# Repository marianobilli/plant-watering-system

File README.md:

# Plant Watering System

An automated 6-plant watering system built on an ESP32-S3 (YD-ESP32-23), designed around the failures of typical DIY irrigation projects: corroding sensors, constant over-watering, no verification that watering worked.

- **6 independent stations:** capacitive moisture sensor + 12 V peristaltic pump each
- **Two-phase watering cycle:** dry cycle (check every N hours, water only at the minimum threshold) then incremental watering with soak time until the target is reached
- **Failsafes:** a plant is stopped and flagged if moisture does not rise after a dose, if the sensor reads shorted/disconnected, or if a float switch reports a low reservoir; one pump runs at a time
- **Sensor longevity:** sensors are only powered (DIS pin) for the ~1 s of each reading
- **Local UI:** 128×64 OLED + rotary encoder + Confirm/Back buttons; all settings persist in flash (NVS)

Firmware and tests are PlatformIO/Arduino; the board is designed in KiCad. Plants start **disabled** on a fresh board: enable each one from the menu after calibrating its sensor and pump.

## Quick start

```bash
pip install platformio            # or use the PlatformIO VS Code extension
# Plug into the board's UART USB-C connector (not the one labelled USB),
# then set upload_port in platformio.ini (e.g. COM3).
pio run -t upload                 # build + flash
pio device monitor                # serial log @ 115200
pio test -e native                # watering-logic tests on your computer (needs gcc/clang)
pio test -e yd_esp32_23           # same tests on the board
```

First-time setup from the OLED menu: **Menu → Plant n → Cal sensor** (air, then water), **Cal pump** (run 30 s into a cup, enter the mL), set Target / Min / Water mL / Soak / Check h, then switch **Enabled** on.

## Repository layout

```
platformio.ini            Board/env config (yd_esp32_23 = firmware, native = host tests)
partitions/               16 MB partition table (do not edit)
src/main.cpp              Hardware glue: sensors, pumps, float switch, OLED menu, NVS config
include/pins.h            Pin map (mirrors the schematic)
lib/PlantLogic/           Hardware-free per-plant state machine + helpers (unit-tested)
lib/RotaryEncoder/        Quadrature encoder driver
test/test_plant_logic/    Unity tests for lib/PlantLogic
hardware/
  BOM.md                  Bill of materials, derived from the schematic
  pcb_print_1to1_A4.pdf   1:1 printable board drawing (A4) for test-fitting parts and the enclosure
  kicad/                  plant_watering.kicad_{sch,pcb,pro} + project symbol/footprint libs
docs/
  WATERING_LOGIC.md       The two-phase algorithm with worked examples
  lessons_learned.md      Research from 50+ failed DIY projects
  archive/                Superseded Arduino UNO R4 POC / single-plant monitor docs
```

## Pin map

| Function | GPIO |
|----------|------|
| Sensors S1–S6 (ADC1) | 1, 2, 7, 8, 9, 10 |
| Sensor DIS (shared, LOW = on) | 11 |
| Pumps 1–6 (MOSFET gates) | 15, 17, 39, 12, 16, 18 |
| Float switch (optional, LOW = reservoir low) | 47 |
| OLED SDA / SCL | 14 / 13 |
| Encoder A / B / push | 5 / 4 / 6 |
| Confirm / Back | 21 / 38 |

> [!WARNING]
> **Leave the ESP board's `IN-OUT` solder jumper open** (no solder bridge). The PCB powers the ESP from the charger through `5Vin` (footprint pad 21, left header, 2nd from the bottom; not GPIO21, which is pad 40). With the jumper open, the on-board diode keeps that 5 V from flowing back into the ESP's USB-C VBUS, so a laptop can stay plugged in for flashing and monitoring while the charger is connected. Bridged, the charger and the laptop's USB 5 V are tied together and current can be pushed back into the laptop's port. If your board arrives bridged, remove the solder. Before first power-up, check with a multimeter in diode mode (board unpowered): USB VBUS → `5Vin` reads a diode drop (~0.2–0.4 V), the reverse reads open.

Header order, antenna end first (matches footprint pads 1–22 / 23–44):

| Header | Pins |
|--------|------|
| P1 (pads 1–22) | 3V3, 3V3, RST, 4, 5, 6, 7, 15, 16, 17, 18, 8, 3, 46, 9, 10, 11, 12, 13, 14, 5Vin, GND |
| P2 (pads 23–44) | GND, TX, RX, 1, 2, 42, 41, 40, 39, 38, 37, 36, 35, 0, 45, 48, 47, 21, 20, 19, GND, GND |

Sensors are on ADC1 because ADC2 cannot be used while WiFi is active. Avoid IO0, 3, 45, 46 (strapping), 19/20 (USB) and 35–37 (octal PSRAM).

## Hardware

See [hardware/BOM.md](hardware/BOM.md). Power is a single 5 V / 2 A USB-C charger, plugged into a panel-mount USB-C socket on the enclosure ([photo](docs/usb-connector.png)) whose two wires (V+, V−) go to J1 (JST-XH 2-pin); an on-board MT3608 boost module makes 12 V for the pumps. Open `hardware/kicad/plant_watering.kicad_pro` in KiCad 10. To order the PCB, see [docs/MANUFACTURING.md](docs/MANUFACTURING.md) (Gerber export, order settings, per-maker hole sizes).

**UI module:** 1.3" 128×64 OLED + EC11 encoder + Back/Confirm buttons on one 64.9 × 35 mm board ([dimensions](docs/oled-rotary-encoder-dimensions.jpg)).

It mounts face-up to the left of the ESP32, turned 90° (header towards the ESP): its 9-pin header plugs into J2 (a 1×9 2.54 mm female socket) and four M3 brass standoffs screw it down through the matching holes in the J2 footprint. An 8.5 mm socket plus the header's 2.5 mm plastic spacer puts the module ~11 mm up, so use M3 × 11 mm standoffs (or 10 mm + a washer); measure your socket and header first. The module's male header must point out of its back; if the pins stick out of the display side, resolder the header. The socket's pin order matches the module silkscreen (CON SDA SCL PSH TRA TRB BAK GND VCC); VCC is 3V3.

**1:1 printout:** [hardware/pcb_print_1to1_A4.pdf](hardware/pcb_print_1to1_A4.pdf) shows the board outline, pads with real drill sizes, silkscreen and part outlines at true scale on A4. Use it to check the space the board needs wherever it will be mounted (enclosure, standoffs, cable and connector clearance, access to the ESP's USB-C port) and to test-fit parts before ordering:

1. Print on A4 at **Actual size / 100 %** (never "Fit to page").
2. Check the scale: the board outline must measure **143 × 112 mm**, and the two ESP pin rows 25.4 mm apart.
3. Glue it onto cardboard or foam board, pierce the pads with a pin and push in the real parts; lay it in the enclosure to check the mounting holes and cable routes.

Regenerate it after any PCB change (from `hardware/kicad/`):
`kicad-cli pcb export pdf --mode-single -l Edge.Cuts,F.Mask,F.SilkS,F.Fab --sp --black-and-white --ibt --scale 1 -o ../pcb_print_1to1_A4.pdf plant_watering.kicad_pcb`

## Test rig (3D print)

Before the real enclosure, an open printed tray holds the PCB and all six pumps so the whole system can be wired and run on the bench. The PCB sits on posts with the pump motors underneath it; two pumps mount on each side and two at the back, so the front with the display and controls stays clear. There is no lid and no reservoir: put the inlet tubes in a bucket.

**Ordering or printing:** use **`case/print/test_rig.stl`** (or `.step`), 1:1 in millimetres, one piece, 152 × 122 × 42 mm, about 90 cm³ (≈ 110 g).

| Process and material | Verdict |
|---|---|
| **FDM, PETG** | Best: tough and cheap. PLA also works, nothing on this part flexes |
| MJF or SLS nylon, PA12 | Fine if ordering from a service |
| SLA / resin | Avoid, the thin walls get brittle |

### Printing on FDM: tell the printer this

The part is designed to print **without supports** in the orientation it is in the file.

| Setting | Value |
|---|---|
| **Orientation** | Base plate flat on the bed, walls and posts pointing up, as in the file |
| **Supports** | **Off.** The motor slots are open at the top and the base windows go through, so there is nothing to support |
| Layer / nozzle | 0.2 mm / 0.4 mm |
| Perimeters | 4 (the 4 mm walls and the 8 mm posts then come out nearly solid) |
| Infill | 20 to 30 % |
| Brim | Optional; helps the tall, thin posts if the bed adhesion is poor |

**Hardware to buy with it:**

| Qty | Part |
|----:|------|
| 12 | M3 male–male rubber anti-vibration mounts, Ø8 × 8 mm ("M3 rubber shock absorber") |
| 24 | M3 nuts |
| 5 | M3 heat-set inserts, 3 mm long × 4.2 mm OD, and 5 × M3 × 5 screws for the PCB |
| 6 | 3 mm foam tape pads, about 16 × 12 mm |
| 4 | Stick-on rubber feet |

**Assembly**

1. Press the heat-set inserts into the five posts with a soldering iron (only MH1–MH4 and MH6 have posts; the side motors pass where MH5 and MH7 would be).
2. Screw a rubber mount into each wall hole, with a nut on the inside. Drop each pump's motor into its U-slot from above, lay the bracket on the mounts' outer studs and fit the nuts. The slot is 3.5 mm wider than the motor can on each side, so the motor touches nothing but rubber. A plain M3 screw and nut also fits, without the vibration isolation.
3. Stick a foam pad on the small block under each motor's free end, so the motor doesn't sag on the rubber.
4. Trim the PCB's through-hole leads to **2 mm or less** on the underside: the motors run 2.5 mm under the trimmed joints. Then screw the PCB onto the posts, display at the open front.
5. Pump numbering follows J9–J14, going round from the front left: **P1, P2** on the left wall (front, back), **P3, P4** on the back wall (left, right), **P5, P6** on the right wall (back, front). The tube stubs point up.

**Regenerating the rig.** The rig is generated by `case/test_rig.py` with [build123d](https://build123d.readthedocs.io/), reading the mounting-hole positions from the KiCad board. Running it rewrites `case/print/`, writes every format to `case/out/` (with a full assembly STEP) and checks the rig and both pump mountings (rubber and direct) against every part on the board. It needs KiCad 10 for `kicad-cli`, Python 3 with `build123d` and `ocp_vscode`, and optionally the *OCP CAD Viewer* extension in VS Code (Ctrl+K V) to see the assembly:

```bash
pip install build123d ocp_vscode
python case/test_rig.py            # pumps on rubber mounts in the viewer
python case/test_rig.py direct     # pumps screwed flat to the walls
```

Every dimension is a parameter at the top of the script, and the pump model comes from [docs/Pump Technical Drawing Views.pdf](docs/Pump%20Technical%20Drawing%20Views.pdf).

## Common DIY mistakes this avoids

| Mistake | Solution here |
|---------|---------------|
| Resistive sensors corrode in weeks | Capacitive sensors, waterproofed with nail polish |
| Sensors always powered | DIS pin: on only while reading |
| Constant watering, root rot | Dry cycle with configurable thresholds |
| Re-watering before moisture spreads | Soak time between doses |
| No check that watering worked | Fault latched if moisture does not rise |
| Pump left running / reservoir empty | Hard 2 min cap per run, float switch stops pumping |

Details: [docs/lessons_learned.md](docs/lessons_learned.md), [docs/WATERING_LOGIC.md](docs/WATERING_LOGIC.md).

## Tuning and best practices

**Soak time** (wait after each dose before re-measuring): sandy/fast-draining soil 3–5 min, loam 5–10 min, clay/slow-draining 10–15 min. Default 5 min.

**Sensors:** capacitive only (resistive ones corrode in weeks), waterproofed with nail polish; calibrate in the real soil, not just air/water; use a TLC555-based sensor on 3.3 V systems, not NE555.

**Mechanical:** keep the reservoir **below** plant level (above it, water keeps siphoning after the pump stops); opaque tubing, 5–6 mm ID (narrower clogs); a closed-end hose with ~1 mm holes at each plant distributes more evenly than Y-splitters; flush with plain water and descale with vinegar when it clogs.

**Maintenance schedule**

| Interval | Task |
|----------|------|
| Weekly | Check reservoir level, test a pump manually, look for odd moisture readings or sensor drift |
| Monthly | Inspect tubing for algae/scale, compare readings with a finger test, check connectors for corrosion |
| Quarterly | Inspect sensor waterproofing, recalibrate if drifting, clean reservoir with vinegar, check MOSFETs/diodes |
| Yearly | **Replace peristaltic pump tubing** (it wears out), deep-clean reservoir and tubing, replace corroded sensors, test failsafes (unplugged sensor, empty reservoir) |

Act immediately if: readings disagree with the soil, a pump runs but no water flows, watering becomes erratic, or you see corrosion on a sensor or wire.

**If WiFi is added later:** the ESP32 does not reliably reconnect on its own, so check `WiFi.status()` in `loop()` and call `WiFi.reconnect()`; use a static IP, a 20 MHz router channel and better than −70 dBm signal. Keep sensors on ADC1 (ADC2 is unusable while WiFi is on). For deep sleep, wait ~500 ms after waking before reading RTC memory and use `1000000ULL` for the timer constant.

## Status

Firmware builds and the watering-logic tests pass. The hardware path (ADC readings, OLED menu, pumps) has **not yet been run on a board**. The earlier single-plant Arduino UNO R4 firmware and docs are kept in `docs/archive/` and in git history.

## TODO

### Before ordering the PCB
- [ ] Check the panel USB-C socket has 5.1 kΩ CC pull-downs built in (needed for C-to-C chargers) and verify V+/V− polarity to J1 (1 GND, 2 VBUS) before plugging in a charger
- [ ] Consider moving the ESP so its antenna overhangs the board edge (needs a full re-route); until then the copper-pour keepout under the antenna is the mitigation
- [ ] Generate Gerbers/drill files (`python hardware/fab/export_fab.py`, see [docs/MANUFACTURING.md](docs/MANUFACTURING.md)) and review them in a viewer before sending to the fab

### Bring-up
- [ ] Set the MT3608 output to **12 V with no pumps connected**, then check the +5 V and +3V3 rails
- [ ] Verify the float switch polarity and wiring (contact closes to GND when the reservoir is low; leave J15 empty if unused)
- [ ] Fit the UI module on J2 with its standoffs (height, hole alignment) and verify its wiring (OLED I2C address and driver: SH1106 vs SSD1306, encoder direction, CON/BAK buttons)
- [ ] Flash and run the firmware on the real board for the first time (the OLED menu, ADC reads, pumps and NVS are untested on hardware)
- [ ] Calibrate each sensor (air/water) and each pump (30 s into a cup); the 12-bit ADC defaults (3100 dry / 1500 wet) are only a guess
- [ ] Check ADC noise and linearity at 11 dB attenuation with the shared DIS line; tune `SENSOR_WARMUP_MS` / `SENSOR_SAMPLES` if readings drift
- [ ] Confirm one pump at a time stays within the 5 V / 2 A charger limit (boost converter input current)
- [ ] Run a monitor-only period with pumps disconnected to learn each plant's dry-down rate before enabling watering
- [ ] Test the failsafes on the bench: unplug a sensor, run a pump dry (no moisture rise), trip the float switch mid-run

### Firmware
- [ ] Run `pio test -e native` and `pio test -e yd_esp32_23` with a real compiler/board (only a one-off host build has been run so far)
- [ ] Log history (moisture per plant) to flash or serial for tuning thresholds
- [ ] Persist the timer state across power loss (checks currently restart on boot)
- [ ] WiFi + remote status/alerts (needs explicit reconnect logic, static IP, ADC1-only sensors)
- [ ] Menu extras: factory reset, per-plant names, rename `Enabled` default flow for first-time setup
- [ ] Set `upload_port` in `platformio.ini` for your machine

### Mechanical / docs
- [x] Open test rig for the PCB and six pumps (`case/test_rig.py`)
- [ ] Enclosure: electronics-and-pump lid on a food-grade 6 L reservoir (waiting on the box's measurements); ultrasonic level sensor; opaque tubing, 5–6 mm ID
- [ ] Waterproof each sensor with 2 coats of clear nail polish before use
- [ ] Write a wiring/assembly guide with photos

## License

[MIT](LICENSE)

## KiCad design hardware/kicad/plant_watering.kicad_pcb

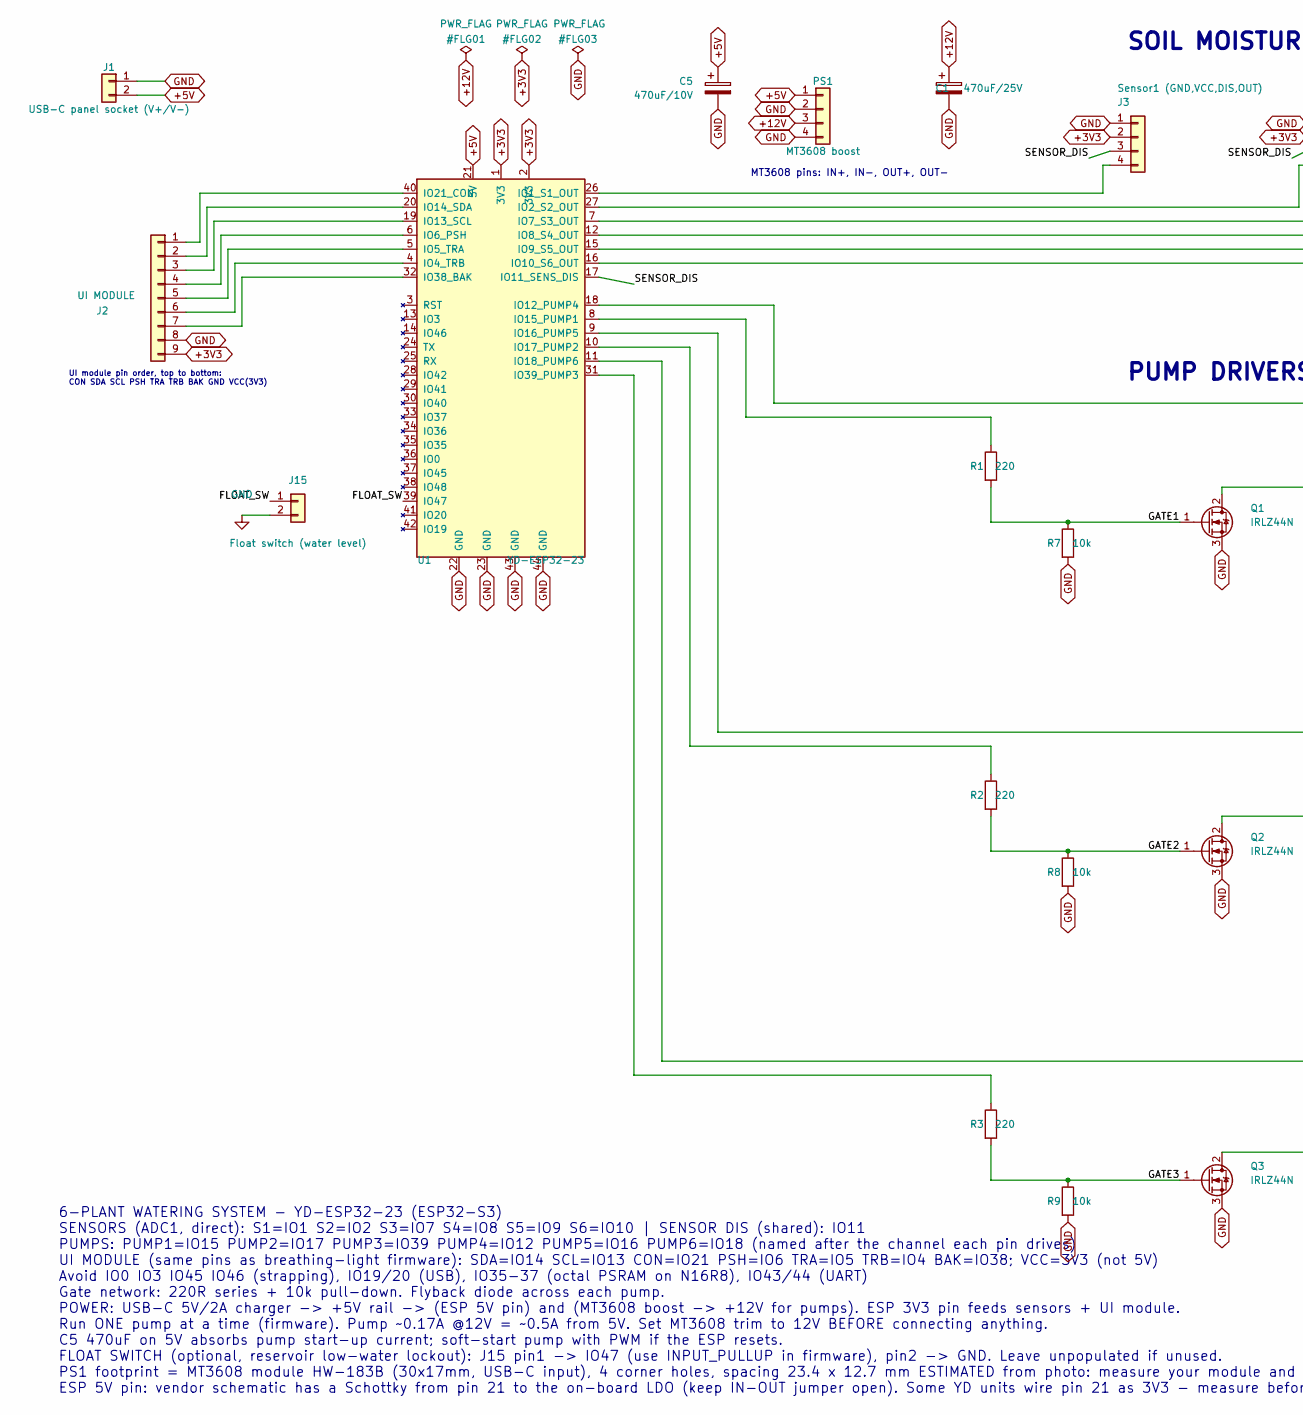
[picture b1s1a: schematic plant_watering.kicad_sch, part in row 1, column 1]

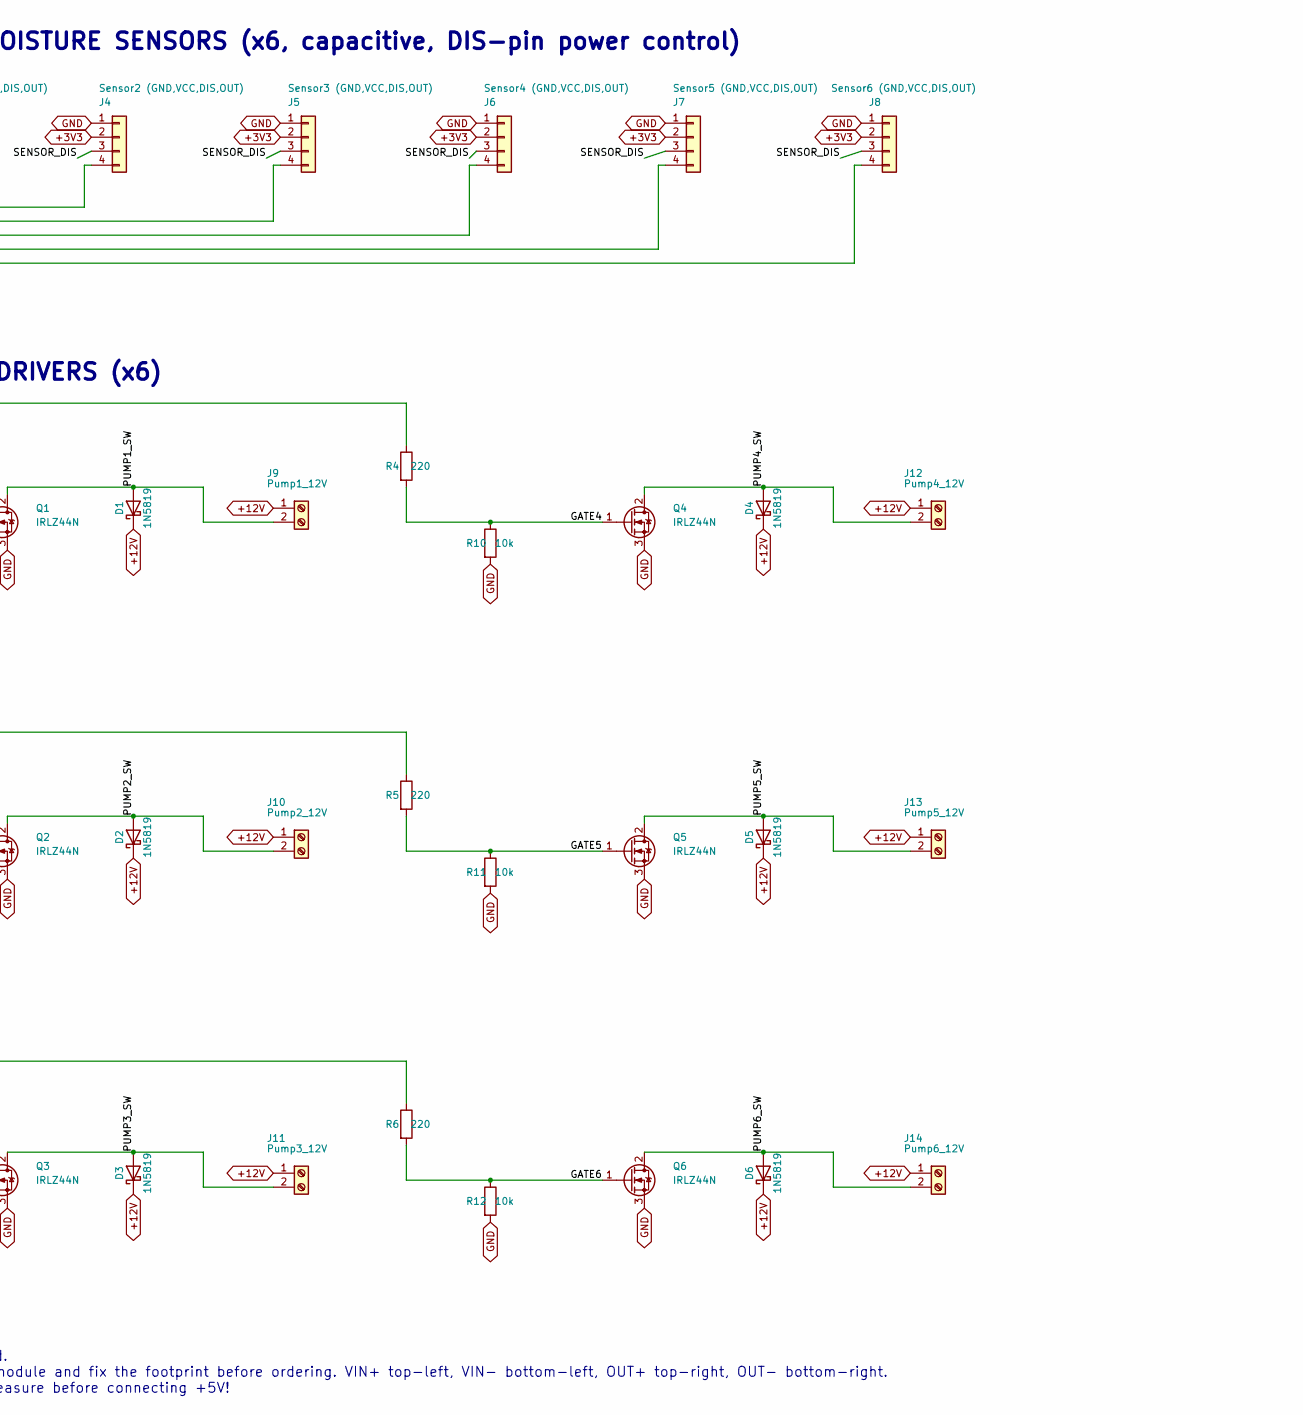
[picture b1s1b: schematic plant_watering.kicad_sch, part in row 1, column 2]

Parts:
C1: 470uF/25V; CP_Radial_D8.0mm_P3.50mm
C5: 470uF/10V; CP_Radial_D8.0mm_P3.50mm
D1, D2, D3, D4, D5, D6: 1N5819; D_DO-41_SOD81_P10.16mm_Horizontal
J1: USB-C panel socket (V+/V-); JST_XH_B2B-XH-A_1x02_P2.50mm_Vertical
J2: UI MODULE; UI_module_OLED_EC11
J3: Sensor1 (GND,VCC,DIS,OUT); JST_XH_B4B-XH-A_1x04_P2.50mm_Vertical
J4: Sensor2 (GND,VCC,DIS,OUT); JST_XH_B4B-XH-A_1x04_P2.50mm_Vertical
J5: Sensor3 (GND,VCC,DIS,OUT); JST_XH_B4B-XH-A_1x04_P2.50mm_Vertical
J6: Sensor4 (GND,VCC,DIS,OUT); JST_XH_B4B-XH-A_1x04_P2.50mm_Vertical
J7: Sensor5 (GND,VCC,DIS,OUT); JST_XH_B4B-XH-A_1x04_P2.50mm_Vertical
J8: Sensor6 (GND,VCC,DIS,OUT); JST_XH_B4B-XH-A_1x04_P2.50mm_Vertical
J9: Pump1_12V; JST_XH_B2B-XH-A_1x02_P2.50mm_Vertical
J10: Pump2_12V; JST_XH_B2B-XH-A_1x02_P2.50mm_Vertical
J11: Pump3_12V; JST_XH_B2B-XH-A_1x02_P2.50mm_Vertical
J12: Pump4_12V; JST_XH_B2B-XH-A_1x02_P2.50mm_Vertical
J13: Pump5_12V; JST_XH_B2B-XH-A_1x02_P2.50mm_Vertical
J14: Pump6_12V; JST_XH_B2B-XH-A_1x02_P2.50mm_Vertical
J15: Float switch (water level); JST_XH_B2B-XH-A_1x02_P2.50mm_Vertical
PS1: MT3608 boost; MT3608_module
Q1, Q2, Q3, Q4, Q5, Q6: IRLZ44N; TO-220-3_Vertical
R1, R2, R3, R4, R5, R6: 220; R_Axial_DIN0207_L6.3mm_D2.5mm_P10.16mm_Horizontal
R7, R8, R9, R10, R11, R12: 10k; R_Axial_DIN0207_L6.3mm_D2.5mm_P10.16mm_Horizontal
U1: YD-ESP32-23

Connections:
+3V3: J2.9, J3.2, J4.2, J5.2, J6.2, J7.2, J8.2, U1.1 (3V3), U1.2 (3V3)
+5V: C5.1, J1.2, PS1.1, U1.21 (5V)
+12V: C1.1, D1.1 (K), D2.1 (K), D3.1 (K), D4.1 (K), D5.1 (K), D6.1 (K), J9.1, J10.1, J11.1, J12.1, J13.1, J14.1, PS1.3
FLOAT_SW: J15.1, U1.39 (IO47)
GATE1: Q1.1 (G), R1.2, R7.1
GATE2: Q2.1 (G), R2.2, R8.1
GATE3: Q3.1 (G), R3.2, R9.1
GATE4: Q4.1 (G), R4.2, R10.1
GATE5: Q5.1 (G), R5.2, R11.1
GATE6: Q6.1 (G), R6.2, R12.1
GND: C1.2, C5.2, J1.1, J2.8, J3.1, J4.1, J5.1, J6.1, J7.1, J8.1, J15.2, PS1.2, PS1.4, Q1.3 (S), Q2.3 (S), Q3.3 (S), Q4.3 (S), Q5.3 (S), Q6.3 (S), R7.2, R8.2, R9.2, R10.2, R11.2, R12.2, U1.22 (GND), U1.23 (GND), U1.43 (GND), U1.44 (GND)
unnamed: J2.1, U1.40 (IO21_CON)
unnamed: J2.2, U1.20 (IO14_SDA)
unnamed: J2.3, U1.19 (IO13_SCL)
unnamed: J2.4, U1.6 (IO6_PSH)
unnamed: J2.5, U1.5 (IO5_TRA)
unnamed: J2.6, U1.4 (IO4_TRB)
unnamed: J2.7, U1.32 (IO38_BAK)
unnamed: J3.4, U1.26 (IO1_S1_OUT)
unnamed: J4.4, U1.27 (IO2_S2_OUT)
unnamed: J5.4, U1.7 (IO7_S3_OUT)
unnamed: J6.4, U1.12 (IO8_S4_OUT)
unnamed: J7.4, U1.15 (IO9_S5_OUT)
unnamed: J8.4, U1.16 (IO10_S6_OUT)
unnamed: R1.1, U1.8 (IO15_PUMP1)
unnamed: R2.1, U1.10 (IO17_PUMP2)
unnamed: R3.1, U1.31 (IO39_PUMP3)
unnamed: R4.1, U1.18 (IO12_PUMP4)
unnamed: R5.1, U1.9 (IO16_PUMP5)
unnamed: R6.1, U1.11 (IO18_PUMP6)
PUMP1_SW: D1.2 (A), J9.2, Q1.2 (D)
PUMP2_SW: D2.2 (A), J10.2, Q2.2 (D)
PUMP3_SW: D3.2 (A), J11.2, Q3.2 (D)
PUMP4_SW: D4.2 (A), J12.2, Q4.2 (D)
PUMP5_SW: D5.2 (A), J13.2, Q5.2 (D)
PUMP6_SW: D6.2 (A), J14.2, Q6.2 (D)
SENSOR_DIS: J3.3, J4.3, J5.3, J6.3, J7.3, J8.3, U1.17 (IO11_SENS_DIS)

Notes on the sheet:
6-PLANT WATERING SYSTEM - YD-ESP32-23 (ESP32-S3) SENSORS (ADC1, direct): S1=IO1 S2=IO2 S3=IO7 S4=IO8 S5=IO9 S6=IO10 | SENSOR DIS (shared): IO11 PUMPS: PUMP1=IO15 PUMP2=IO17 PUMP3=IO39 PUMP4=IO12 PUMP5=IO16 PUMP6=IO18 (named after the channel each pin drives) UI MODULE (same pins as breathing-light 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
PUMP DRIVERS (x6)
UI module pin order, top to bottom: CON SDA SCL PSH TRA TRB BAK GND VCC(3V3)
MT3608 pins: IN+, IN-, OUT+, OUT-
SOIL MOISTURE SENSORS (x6, capacitive, DIS-pin power control)

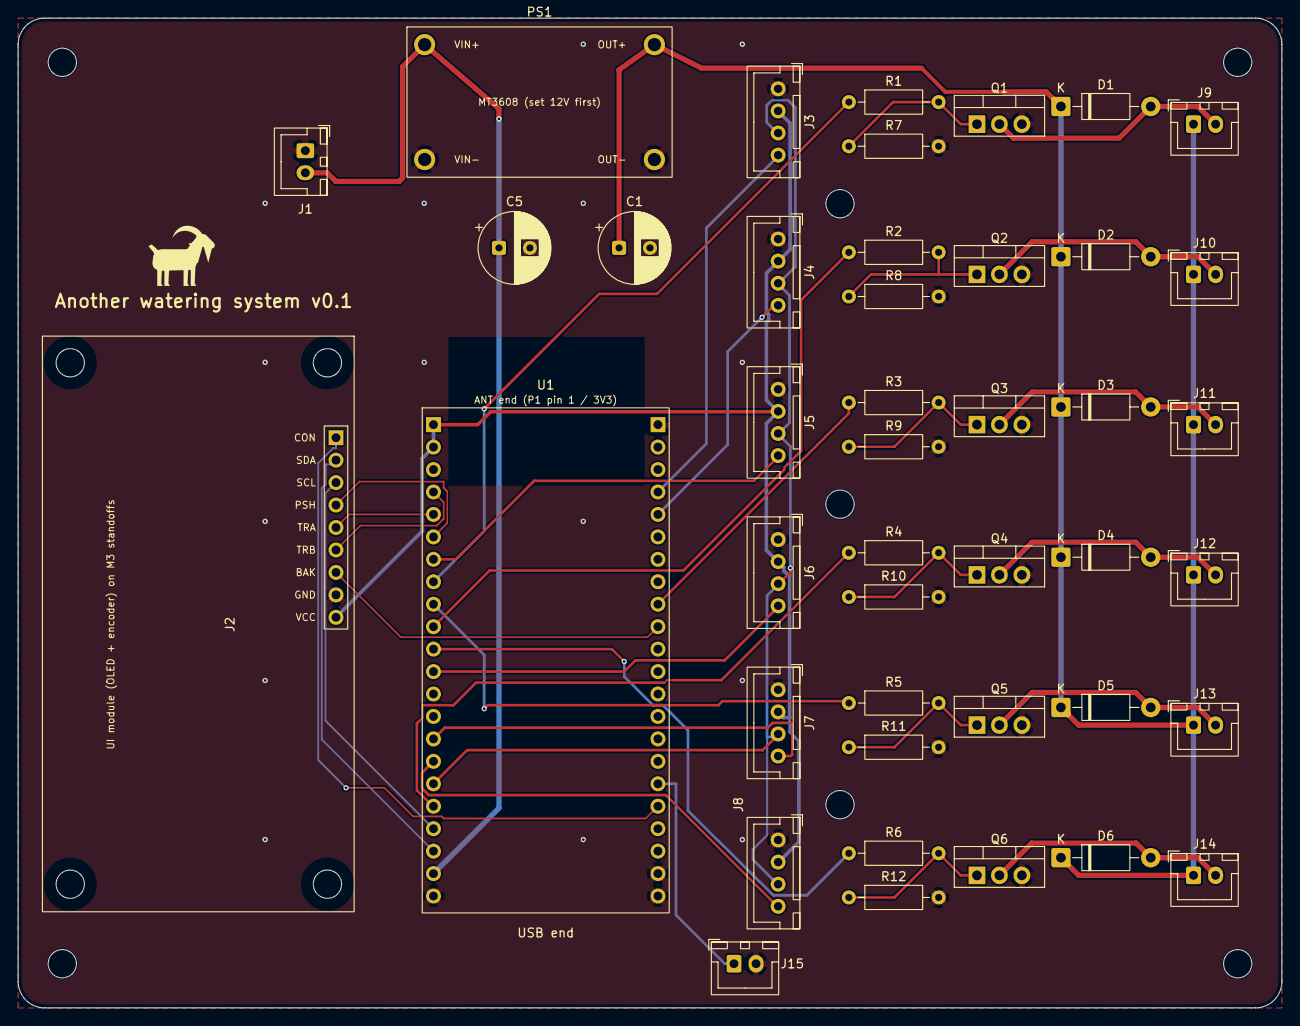
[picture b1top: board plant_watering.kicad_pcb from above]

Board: 2 copper layers, 143.0 x 112.0 mm, 50 parts (0 on the bottom side), 37 nets.

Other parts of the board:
MH1, MH2, MH3, MH4, MH5, MH6, MH7: MountingHole_3.2mm_M3

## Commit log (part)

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2025-12-27 Update README with three-stage development plan
    - Added project evolution overview (POC → Prototype → Final)
    - Stage 1: 2 plants, breadboard, local control only
    - Stage 2: 4 plants, Arduino Cloud integration, mobile app
    - Stage 3: 6 plants, Arduino Nano, 3D printed enclosure
    - Documented Arduino Cloud features: push notifications, multi-user, multi-system
    - Added detailed cloud setup instructions
2025-12-29 Initial version
2026-01-01 monitor only functionality
2026-01-02 monitor functionality v1.0
2026-01-02 folder refactor is a need for arduino ide
2026-01-02 Sensor reading stability
2026-01-04 v1.5
2026-03-01 Project cleanup: watering firmware only
    - Remove monitor firmware, KiCad PCB, docs/, src/ POC, and superseded docs
    - Rename BOM_POC.md → BOM.md
    - Rewrite README with schematic, badges, and design decisions table
    - Update MENU_DESIGN.md to match v1.1 firmware (defaults, state machine, EEPROM map)
    - Condense LESSONS_DEEP_RESEARCH.md by ~50%
    - Add LICENSE (MIT)
